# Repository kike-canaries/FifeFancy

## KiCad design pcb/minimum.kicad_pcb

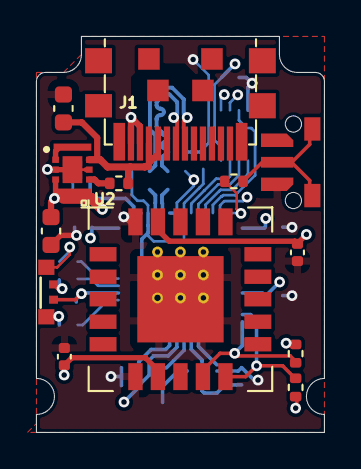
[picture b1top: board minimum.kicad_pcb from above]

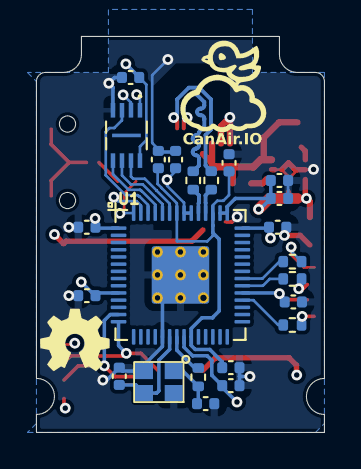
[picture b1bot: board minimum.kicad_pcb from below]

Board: 4 copper layers, 16.0 x 22.0 mm, 38 parts (25 on the bottom side), 28 nets.

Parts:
C1, C2, C3, C4, C5, C6, C7, C9, C12, C13, C16: 100n; C_0402_1005Metric
C8: 4.7u; C_0402_1005Metric
C10, C11: 1u; C_0402_1005Metric
C14, C15: 27p; C_0402_1005Metric
C17, C18: 10u; C_0603_1608Metric
D1: LED_BARG; RGB_LED_3x1
J1: DX07P024MJ1R1500; USB_C_Plug_UTC009-C12
LOGO1: LOGO; CanAir_IO
LOGO2: Logo_Open_Hardware_Small; OHW_LOGO
R1, R2: 27.4; R_0402_1005Metric
R3, R4: 2.2k; R_0402_1005Metric
R5, R6: 1k; R_0402_1005Metric
R7: 10k; R_0402_1005Metric
R8, R9, R10: 470; R_0402_1005Metric
SW1: SW_Push; TL3340AF160QG
U1: RP2040; RP2040-QFN-56
U2: SCD4x; QFN-20_EP_10.1x10.1_Pitch1.25mm
U3: W25Q16JVUXIQ
U4: XCL220
Y1: C2E-12.000-18-1020-X-R; AKER_C2E

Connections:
+1V1: C11.1, C12.1, C13.1, U1.23 (DVDD), U1.45 (VREG_VOUT), U1.50 (DVDD)
+3V3: C1.1, C2.1, C3.1, C4.1, C5.1, C6.1, C7.1, C8.1, C9.1, C10.1, C16.1, C18.1, D1.2 (A), R3.1, R4.1, U1.1 (IOVDD), U1.10 (IOVDD), U1.22 (IOVDD), U1.33 (IOVDD), U1.42 (IOVDD), U1.43 (ADC_AVDD), U1.44 (VREG_IN), U1.48 (USB_VDD), U1.49 (IOVDD), U2.7 (VDD), U2.19 (VDDH), U3.8 (VCC), U4.3 (Vout), U4.8 (L2)
/LED_B: R10.1, U1.32 (GPIO21)
/LED_G: R9.1, U1.35 (GPIO23)
/LED_R: R8.1, U1.34 (GPIO22)
/Pi_USB_D+: R1.2, U1.47 (USB_DP)
/Pi_USB_D-: R2.1, U1.46 (USB_DM)
/QSPI_SCLK: U1.52 (QSPI_SCLK), U3.6 (CLK)
/QSPI_SD0: U1.53 (QSPI_SD0), U3.5 (DI_IO0)
/QSPI_SD1: U1.55 (QSPI_SD1), U3.2 (DO_IO1)
/QSPI_SD2: U1.54 (QSPI_SD2), U3.3 (IO2)
/QSPI_SD3: U1.51 (QSPI_SD3), U3.7 (IO3)
/QSPI_SS: R6.2, U1.56 (QSPI_SS), U3.1 (CS)
/SCL: R3.2, U1.14 (GPIO11), U2.9 (SCL)
/SDA: R4.2, U1.13 (GPIO10), U2.10 (SDA)
/USB_D+: J1.A6 (DA+), R1.1
/USB_D-: J1.A7 (DA-), R2.2
/XIN: C14.2, U1.20 (XIN), Y1.3
/XOUT: R5.2, U1.21 (XOUT)
/XOUTc: C15.2, R5.1, Y1.1
GND: C1.2, C2.2, C3.2, C4.2, C5.2, C6.2, C7.2, C8.2, C9.2, C10.2, C11.2, C12.2, C13.2, C14.1, C15.1, C16.2, C17.2, C18.2, J1.A1 (GNDA), J1.B12 (GNDB), SW1.1, U1.19 (TESTEN), U1.57 (GND), U2.6 (GND), U2.20 (GND), U2.21 (GND), U3.4 (GND), U4.2 (AGND), U4.5 (PGND), U4.PAD, Y1.2, Y1.4
unnamed: D1.1 (BK), R10.2
unnamed: D1.3 (RK), R8.2
unnamed: D1.4 (GK), R9.2
unnamed: R6.1, SW1.2
unnamed: R7.2, U4.4 (CE)
unnamed: U4.1 (Lx), U4.7 (L1)
VBUS: C17.1, J1.A4 (A_VBUS), J1.B9 (B_VBUS), R7.1, U4.6 (Vin)

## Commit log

2021-09-01 flash added
2021-09-01 connecting signals
2021-09-02 flash changed due to space constrains
2021-09-02 HIDING LABELS
2021-09-03 routing
2021-09-03 missing libs added
2021-09-05 USB plug connector changed to DX07P024MJ1R1500
2021-09-05 routing VBUS
2021-09-05 adding led and push button libs
2021-09-05 OH logo added
2021-09-06 changing the USB connector following the recommendation of arturo182
2021-09-06 DRC OK
2021-09-06 CanAir.IO logo added
2021-09-06 OpenHardware logo added
2021-09-06 useless fixes :/
2021-09-06 Fix common pin RGB Led
2021-09-07 solder past fixed
2021-09-07 fabrication files

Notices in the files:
parts and their libraries:
Copyright 2021 Accelerated Designs. All rights reserved.
